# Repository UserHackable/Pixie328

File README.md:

## Pixie 328

This is a very bare minimum breadboard Arduino board. 

It uses a standard FTDI connector on one end to program the ATtiny85 Micro controller with, and has a ICSP header to burn the boot loader on the other end. 

It also has a place for a ceramic frequency clock, and an optional reset pullup resistor. 

The pull-up resistor is optional, as the internal pull-up will work, unless you expressly turn it off. 

Bare minimum, and inspired by Dale Wheat's breadboard Arduino. 

## Pixie328 

### Board dimensions

* (200000, 80000) original units
* (2.0000, 0.8000) inches
* (50.8000, 20.3200) mm

| Front | Back |
| --- | --- |
|  |  |

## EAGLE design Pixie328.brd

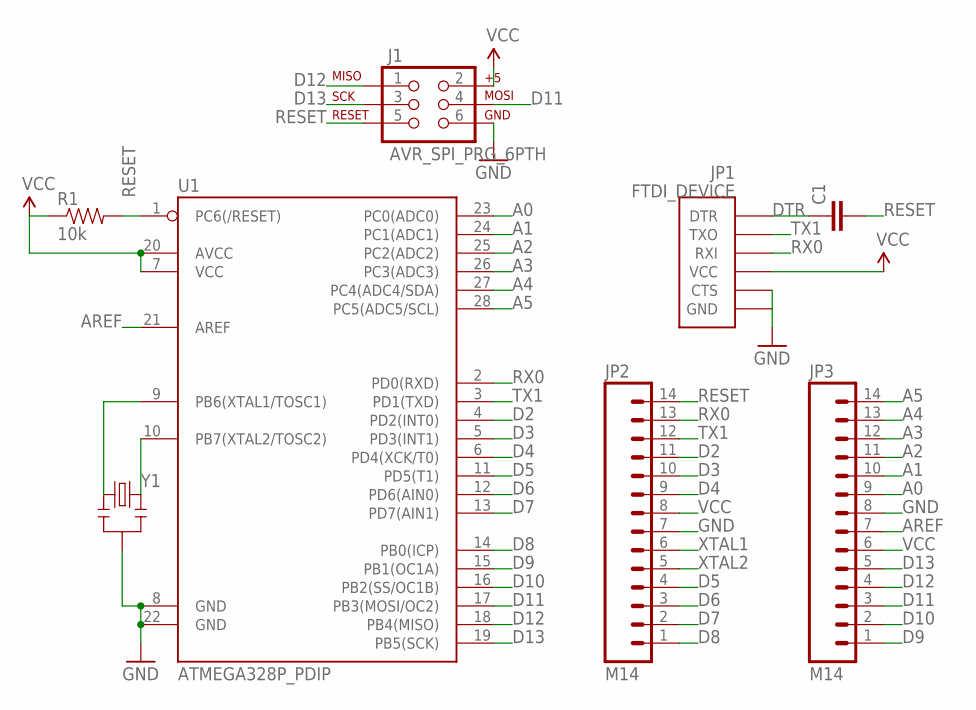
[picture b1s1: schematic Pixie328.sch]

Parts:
C1: CAPEZ; CAP-PTH-SMALLEZ
J1: AVR_SPI_PRG_6PTH; 2X3
JP1: FTDI_DEVICE; FTDI_DEVICE_SIDE
JP2, JP3: M14; 1X14
R1: 10k; AXIAL-0.3
U1: ATMEGA328P_PDIP; DIL28-3
Y1: RESONATORPTH; RESONATOR-PTH

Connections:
A0: JP3.9, U1.23 (PC0(ADC0))
A1: JP3.10, U1.24 (PC1(ADC1))
A2: JP3.11, U1.25 (PC2(ADC2))
A3: JP3.12, U1.26 (PC3(ADC3))
A4: JP3.13, U1.27 (PC4(ADC4/SDA))
A5: JP3.14, U1.28 (PC5(ADC5/SCL))
AREF: JP3.7, U1.21 (AREF)
D2: JP2.11, U1.4 (PD2(INT0))
D3: JP2.10, U1.5 (PD3(INT1))
D4: JP2.9, U1.6 (PD4(XCK/T0))
D5: JP2.4, U1.11 (PD5(T1))
D6: JP2.3, U1.12 (PD6(AIN0))
D7: JP2.2, U1.13 (PD7(AIN1))
D8: JP2.1, U1.14 (PB0(ICP))
D9: JP3.1, U1.15 (PB1(OC1A))
D10: JP3.2, U1.16 (PB2(SS/OC1B))
D11: J1.4, JP3.3, U1.17 (PB3(MOSI/OC2))
D12: J1.1, JP3.4, U1.18 (PB4(MISO))
D13: J1.3, JP3.5, U1.19 (PB5(SCK))
DTR: C1.1, JP1.P$1 (DTR)
GND: J1.6, JP1.P$5 (CTS), JP1.P$6 (GND), JP2.7, JP3.8, U1.8 (GND), U1.22 (GND), Y1.2
RESET: C1.2, J1.5, JP2.14, R1.P$2 (2), U1.1 (PC6(/RESET))
RX0: JP1.P$3 (RXI), JP2.13, U1.2 (PD0(RXD))
TX1: JP1.P$2 (TXO), JP2.12, U1.3 (PD1(TXD))
VCC: J1.2, JP1.P$4 (VCC), JP2.8, JP3.6, R1.P$1 (1), U1.7 (VCC), U1.20 (AVCC)
XTAL1: JP2.6, U1.9 (PB6(XTAL1/TOSC1)), Y1.1
XTAL2: JP2.5, U1.10 (PB7(XTAL2/TOSC2)), Y1.3

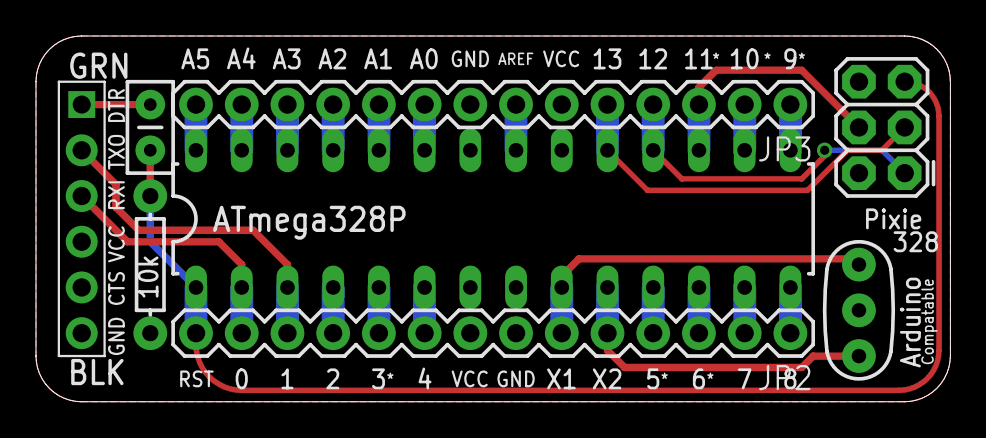
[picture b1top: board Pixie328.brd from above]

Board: 2 copper layers, 50.8 x 20.3 mm, 8 parts (0 on the bottom side), 27 nets.

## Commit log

2016-04-08 from Makefile

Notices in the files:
parts and their libraries:
SparkFun-Connectors: Licensing: Creative Commons ShareAlike 4.0 International - https://creativecommons.org/licenses/by-sa/4.0
